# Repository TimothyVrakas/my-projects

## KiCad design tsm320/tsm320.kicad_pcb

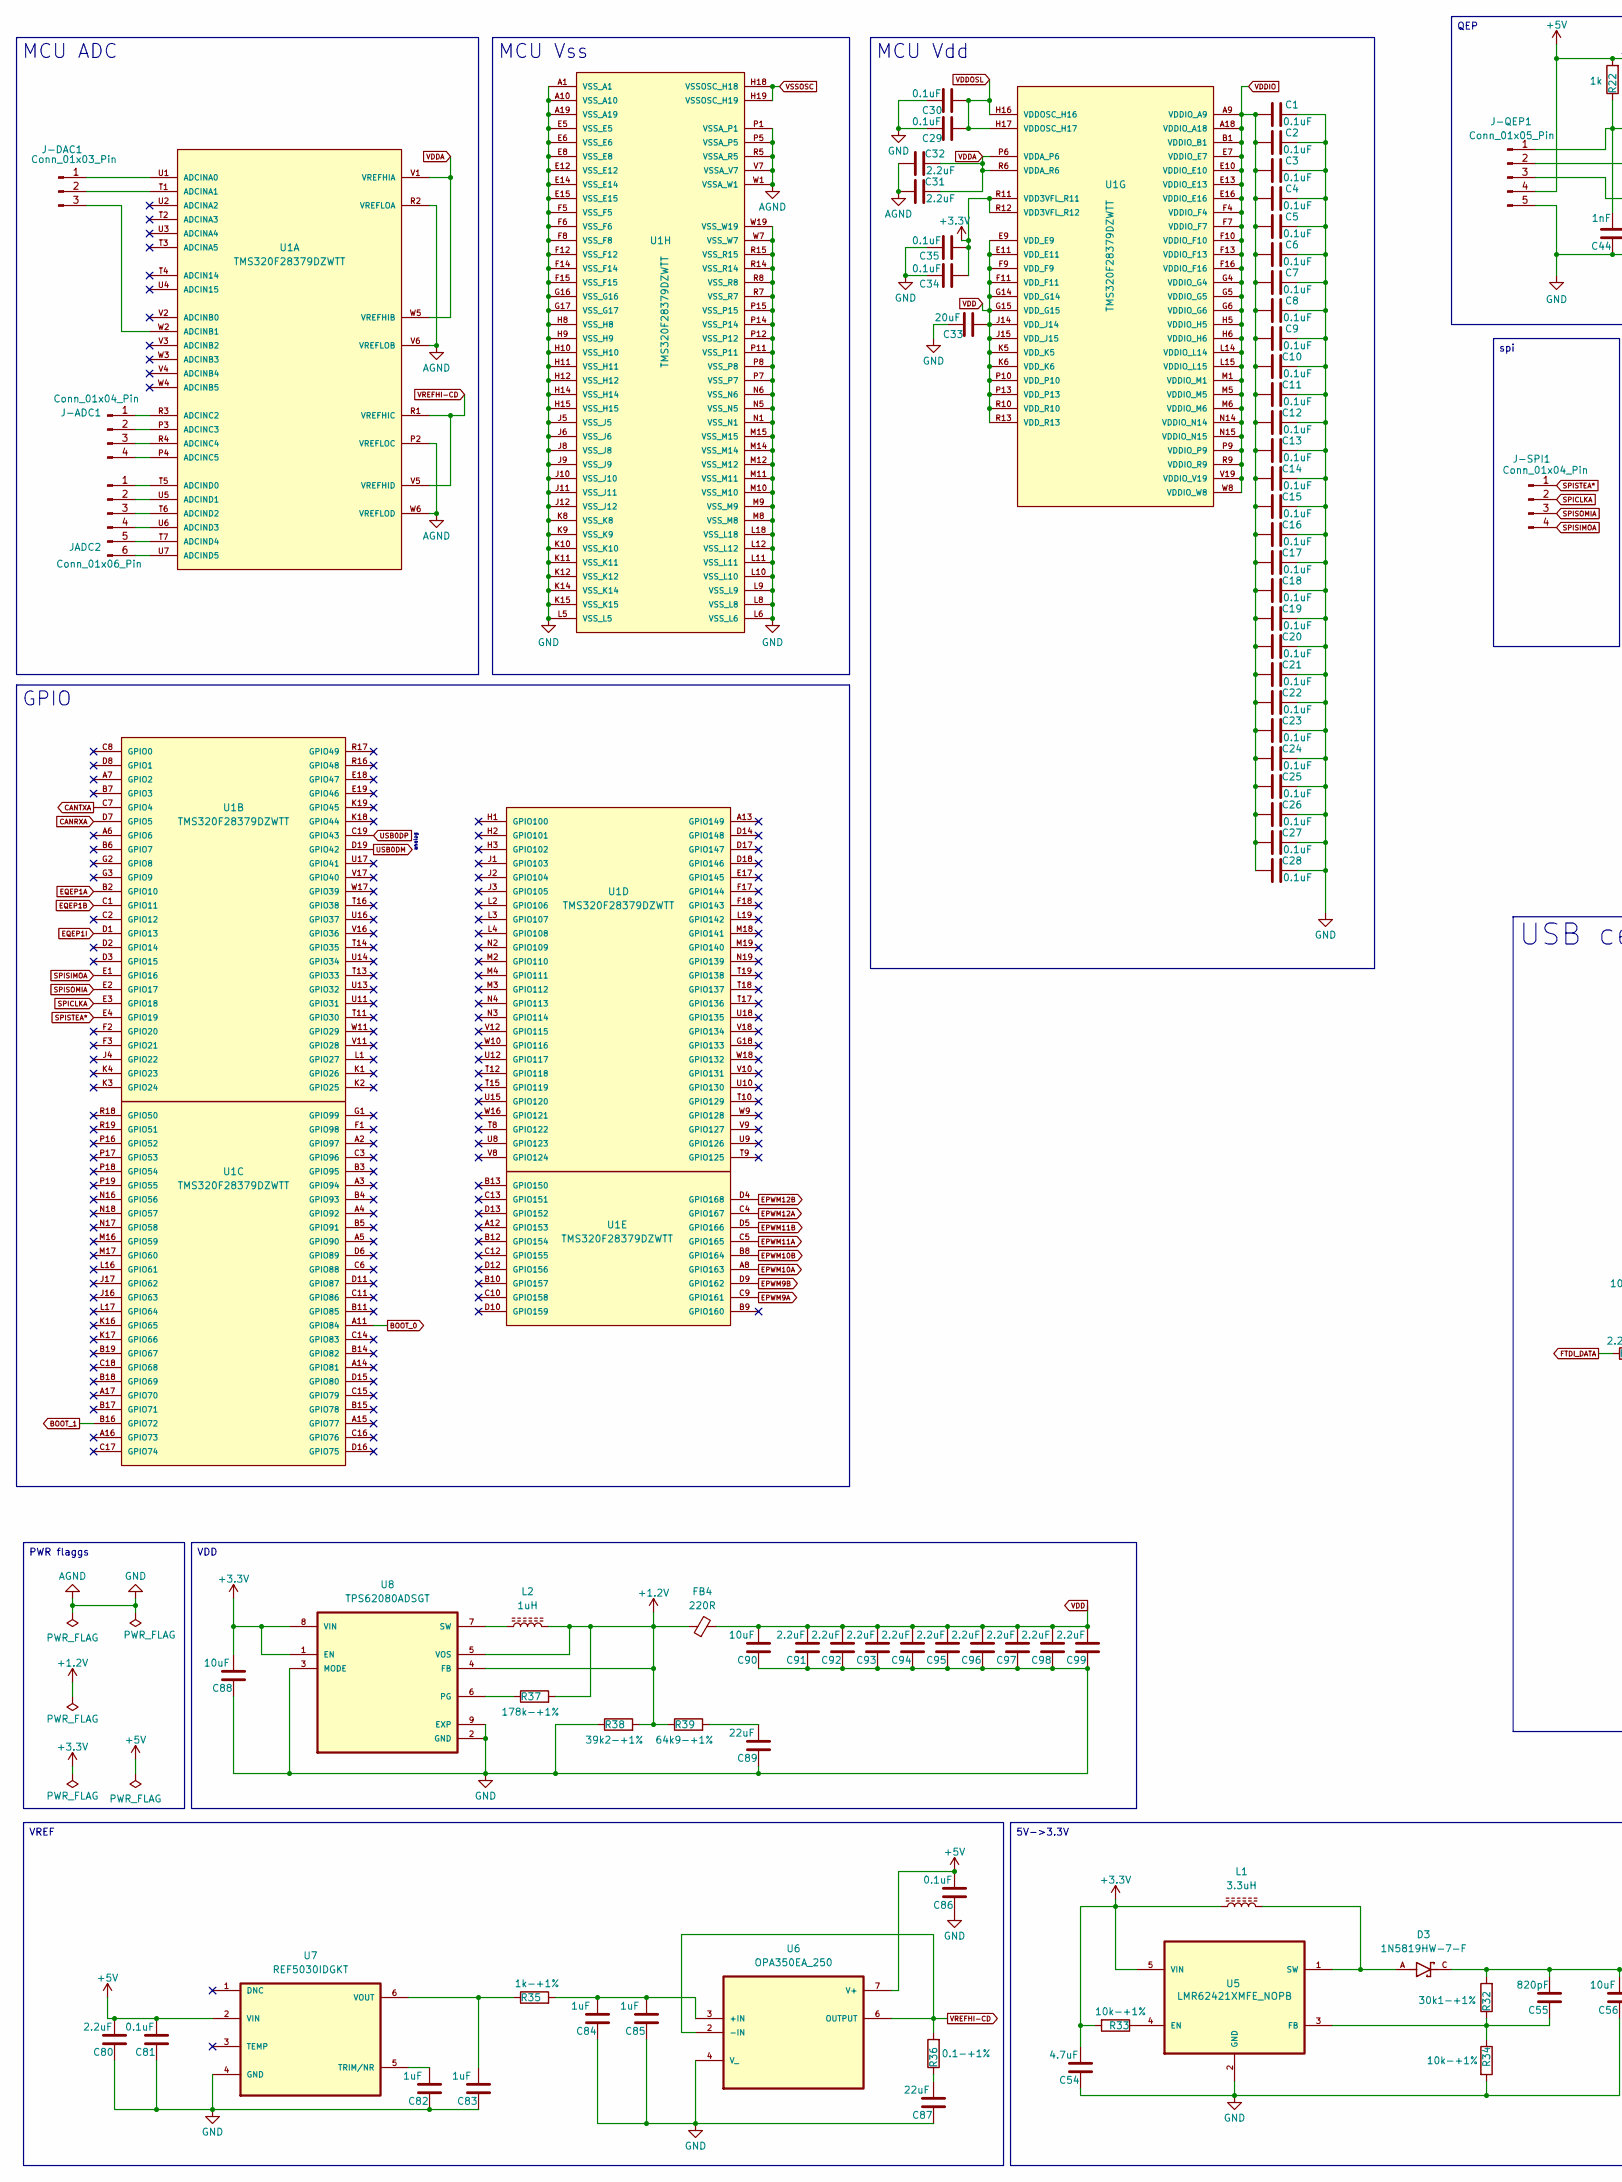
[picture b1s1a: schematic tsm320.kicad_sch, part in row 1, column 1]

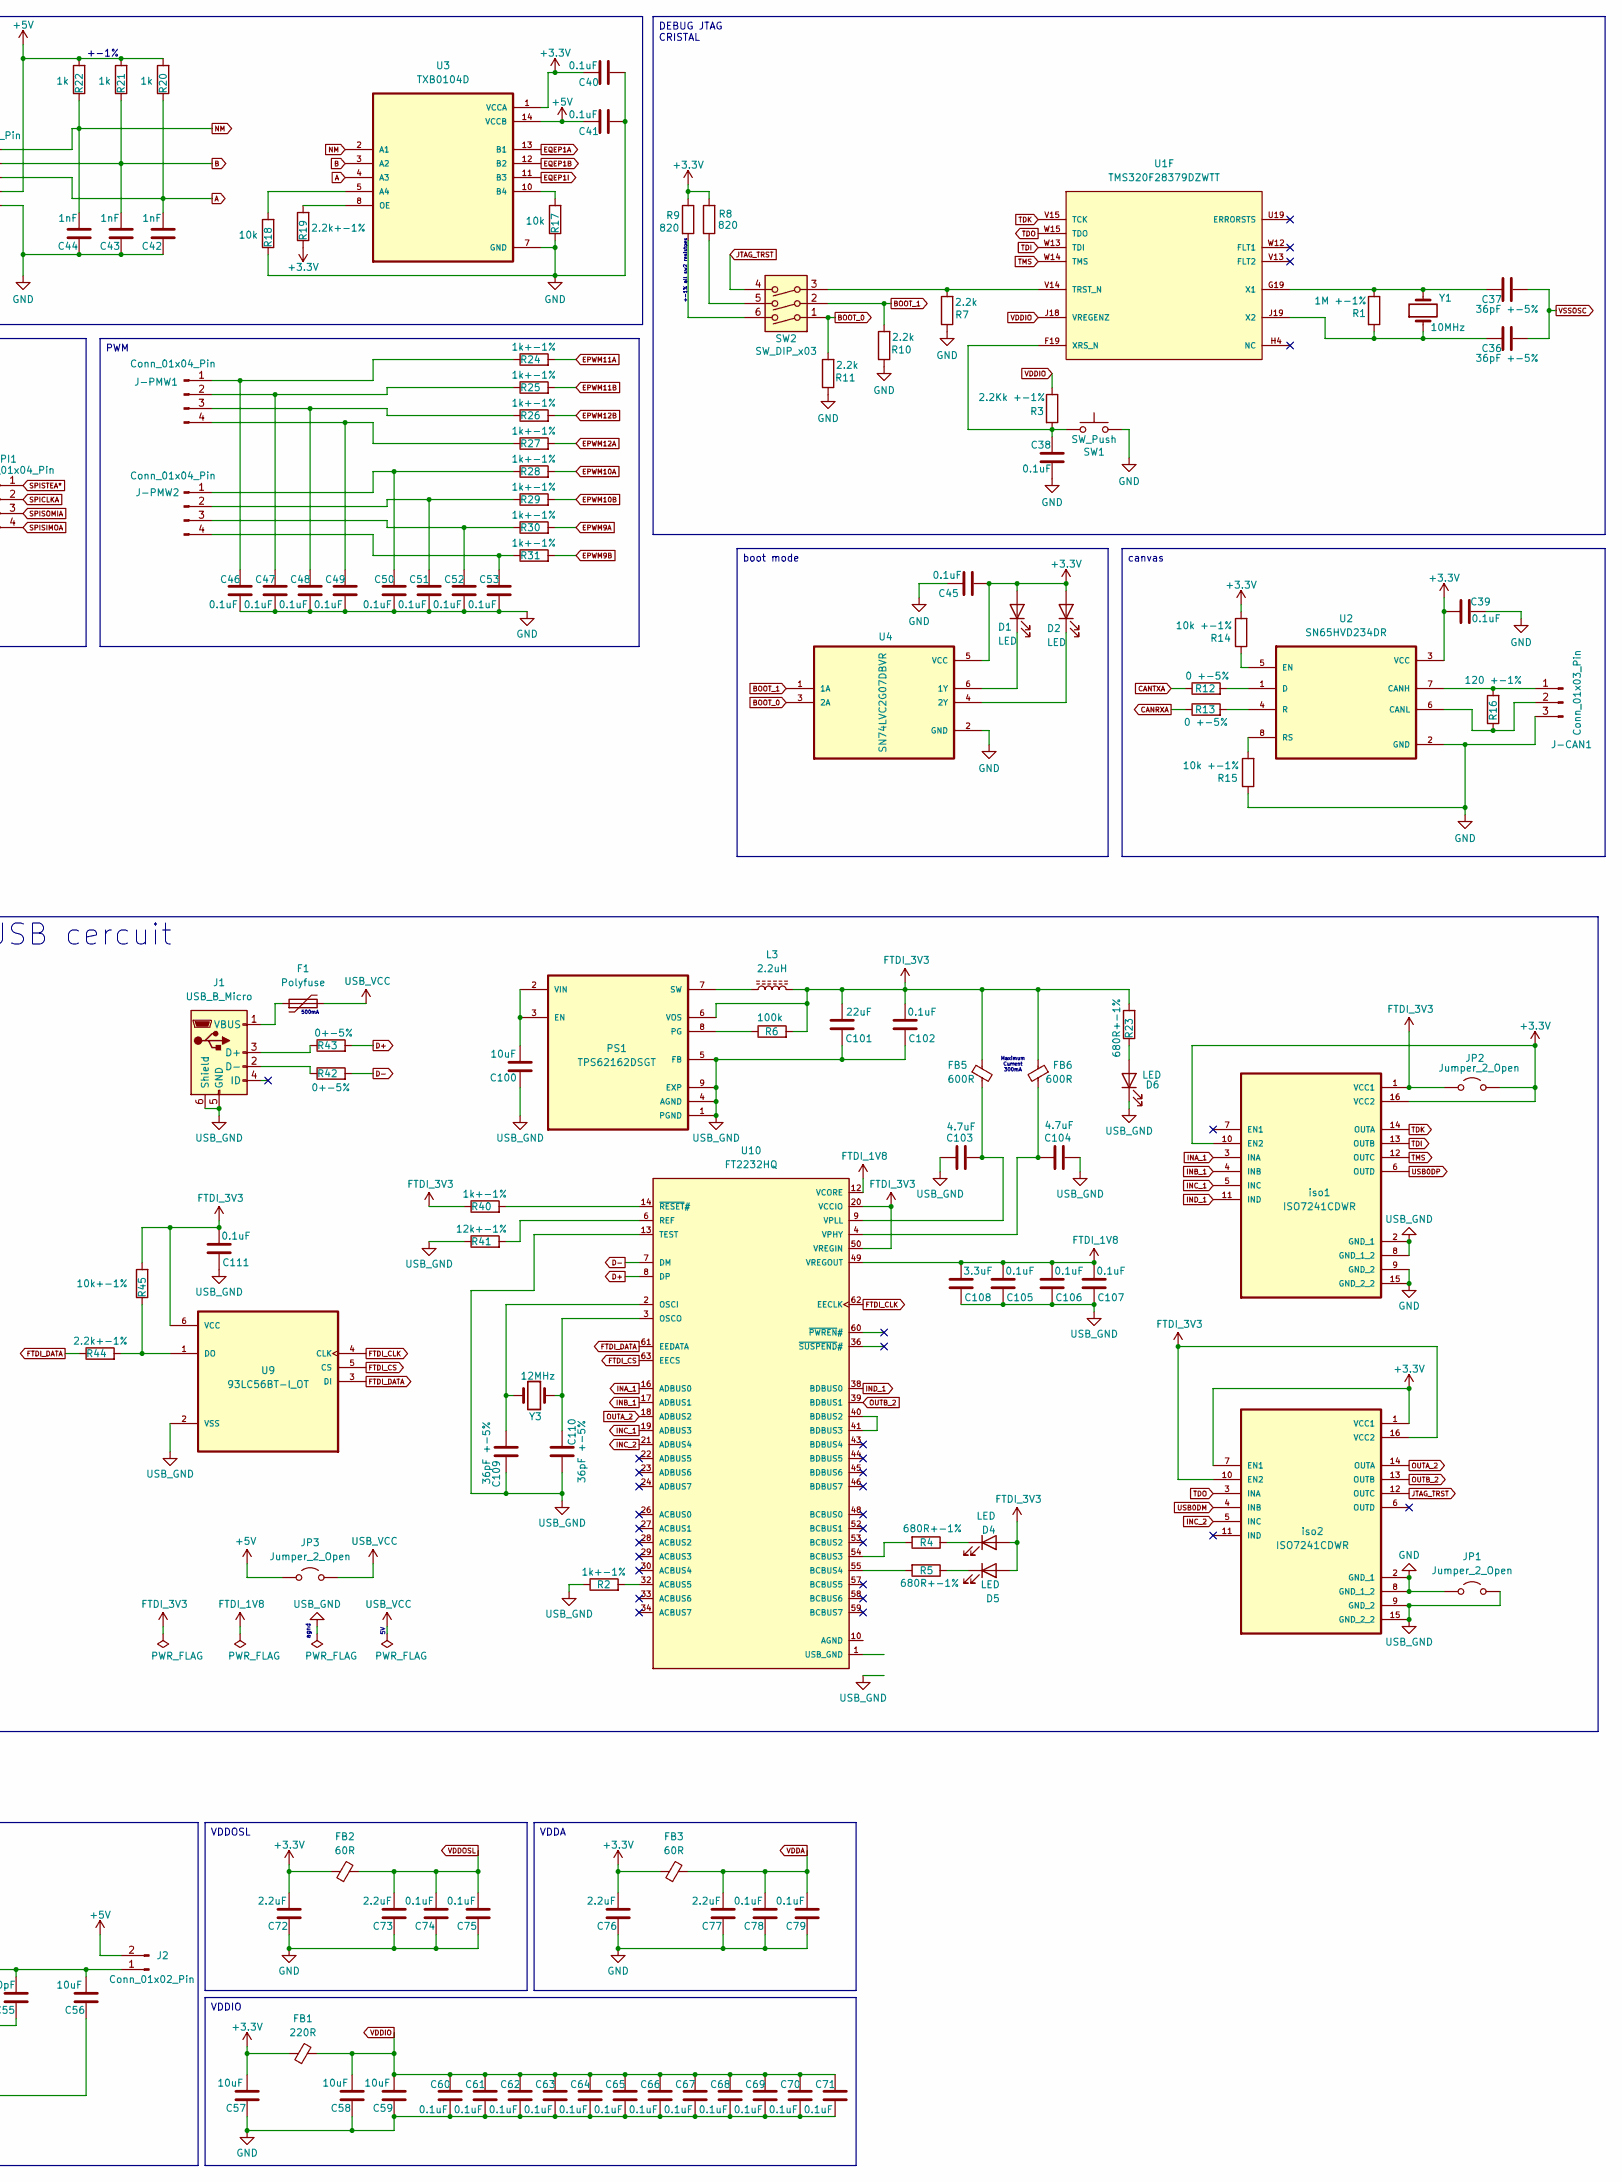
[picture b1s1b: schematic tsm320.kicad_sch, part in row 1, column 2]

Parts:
C1, C2, C3, C4, C5, C6, C7, C8, C9, C10, C11, C12, C13, C14, C15, C16, C17, C18, C19, C20, C21, C22, C23, C24, C25, C26, C27, C28, C29, C30, C34, C35, C38, C39, C40, C41, C45, C46, C47, C48, C49, C50, C51, C52, C53, C60, C61, C62, C63, C64, C65, C66, C67, C68, C69, C70, C71, C74, C75, C78, C79, C81, C86, C102, C105, C106, C107, C111: 0.1uF; C_0805_2012Metric_Pad1.18x1.45mm_HandSolder
C31, C32, C72, C73, C76, C77, C80, C91, C92, C93, C94, C95, C96, C97, C98, C99: 2.2uF; C_0805_2012Metric_Pad1.18x1.45mm_HandSolder
C33: 20uF; C_0805_2012Metric_Pad1.18x1.45mm_HandSolder
C36, C37, C109, C110: 36pF +-5%; C_0805_2012Metric_Pad1.18x1.45mm_HandSolder
C42, C43, C44: 1nF; C_0805_2012Metric_Pad1.18x1.45mm_HandSolder
C54, C103, C104: 4.7uF; C_0805_2012Metric_Pad1.18x1.45mm_HandSolder
C55: 820pF; C_0805_2012Metric_Pad1.18x1.45mm_HandSolder
C56, C57, C58, C59, C88, C90, C100: 10uF; C_0805_2012Metric_Pad1.18x1.45mm_HandSolder
C82, C83, C84, C85: 1uF; C_0805_2012Metric_Pad1.18x1.45mm_HandSolder
C87, C89, C101: 22uF; C_0805_2012Metric_Pad1.18x1.45mm_HandSolder
C108: 3.3uF; C_0805_2012Metric_Pad1.18x1.45mm_HandSolder
D1, D2, D4, D5, D6: LED; LED_0805_2012Metric_Pad1.15x1.40mm_HandSolder
D3: 1N5819HW-7-F; SOD3715X145N; PARTREV 18-2
F1: Polyfuse; FUSM4632X85
FB1, FB4: 220R; L_0805_2012Metric_Pad1.05x1.20mm_HandSolder
FB2, FB3: 60R; L_0805_2012Metric_Pad1.05x1.20mm_HandSolder
FB5, FB6: 600R; L_0805_2012Metric_Pad1.05x1.20mm_HandSolder
J1: USB_B_Micro; TE_1-1734328-2
J2: Conn_01x02_Pin; PinHeader_1x02_P2.54mm_Vertical
J-ADC1: Conn_01x04_Pin; PinHeader_1x04_P2.54mm_Vertical
J-CAN1: Conn_01x03_Pin; PinHeader_1x03_P2.54mm_Vertical
J-DAC1: Conn_01x03_Pin; PinHeader_1x03_P2.54mm_Vertical
J-PMW1, J-PMW2: Conn_01x04_Pin; PinHeader_1x04_P2.54mm_Vertical
J-QEP1: Conn_01x05_Pin; PinHeader_1x05_P2.54mm_Vertical
J-SPI1: Conn_01x04_Pin; PinHeader_1x04_P2.54mm_Vertical
JADC2: Conn_01x06_Pin; PinHeader_1x06_P2.54mm_Vertical
JP1, JP2, JP3: Jumper_2_Open; TestPoint_2Pads_Pitch2.54mm_Drill0.8mm
L1: 3.3uH; L_0805_2012Metric_Pad1.05x1.20mm_HandSolder
L2: 1uH; L_0805_2012Metric_Pad1.05x1.20mm_HandSolder
L3: 2.2uH; L_0805_2012Metric_Pad1.05x1.20mm_HandSolder
PS1: TPS62162DSGT; SON50P200X200X80-9N; PARTREV E
R1: 1M +-1%; R_0805_2012Metric_Pad1.20x1.40mm_HandSolder
R2, R24, R25, R26, R27, R28, R29, R30, R31, R40: 1k+-1%; R_0805_2012Metric_Pad1.20x1.40mm_HandSolder
R3: 2.2Kk +-1%; R_0805_2012Metric_Pad1.20x1.40mm_HandSolder
R4, R5, R23: 680R+-1%; R_0805_2012Metric_Pad1.20x1.40mm_HandSolder
R6: 100k; R_0805_2012Metric_Pad1.20x1.40mm_HandSolder
R7, R10, R11: 2.2k; R_0805_2012Metric_Pad1.20x1.40mm_HandSolder
R8, R9: 820; R_0805_2012Metric_Pad1.20x1.40mm_HandSolder
R12, R13: 0 +-5%; R_0805_2012Metric_Pad1.20x1.40mm_HandSolder
R14, R15: 10k +-1%; R_0805_2012Metric_Pad1.20x1.40mm_HandSolder
R16: 120 +-1%; R_0805_2012Metric_Pad1.20x1.40mm_HandSolder
R17, R18: 10k; R_0805_2012Metric_Pad1.20x1.40mm_HandSolder
R19, R44: 2.2k+-1%; R_0805_2012Metric_Pad1.20x1.40mm_HandSolder
R20, R21, R22: 1k; R_0805_2012Metric_Pad1.20x1.40mm_HandSolder
R32: 30k1-+1%; R_0805_2012Metric_Pad1.20x1.40mm_HandSolder
R33, R34: 10k-+1%; R_0805_2012Metric_Pad1.20x1.40mm_HandSolder
R35: 1k-+1%; R_0805_2012Metric_Pad1.20x1.40mm_HandSolder
R36: 0.1-+1%; R_0805_2012Metric_Pad1.20x1.40mm_HandSolder
R37: 178k-+1%; R_0805_2012Metric_Pad1.20x1.40mm_HandSolder
R38: 39k2-+1%; R_0805_2012Metric_Pad1.20x1.40mm_HandSolder
R39: 64k9-+1%; R_0805_2012Metric_Pad1.20x1.40mm_HandSolder
R41: 12k+-1%; R_0805_2012Metric_Pad1.20x1.40mm_HandSolder
R42, R43: 0+-5%; R_0805_2012Metric_Pad1.20x1.40mm_HandSolder
R45: 10k+-1%; R_0805_2012Metric_Pad1.20x1.40mm_HandSolder
SW1: SW_Push; B3F3152
SW2: SW_DIP_x03; SW3_219-3MST_CTS
U1: TMS320F28379DZWTT; BGA337C80P19X19_1600X1600X140N; PARTREV M; DigiKey_Part_Number 296-48453-ND
U2: SN65HVD234DR; SOIC127P600X175-8N
U3: TXB0104D; SOIC127P600X175-14N; DigiKey_Part_Number 296-34698-5-ND
U4: SN74LVC2G07DBVR; SOT95P280X145-6N
U5: LMR62421XMFE_NOPB; SOT95P280X145-5N
U6: OPA350EA_250; SOP65P490X110-8N
U7: REF5030IDGKT; SOP65P490X110-8N
U8: TPS62080ADSGT; SON50P200X200X80-9N; PARTREV F; DigiKey_Part_Number 296-30360-1-ND
U9: 93LC56BT-I_OT; SOT95P280X145-6N
U10: FT2232HQ; QFN50P900X900X100-65N
Y1: 10MHz; Crystal_SMD_HC49-SD_HandSoldering
Y3: 12MHz; Crystal_SMD_HC49-SD_HandSoldering
iso1, iso2: ISO7241CDWR; SOIC127P1030X265-16N

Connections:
+1.2V: FB4.1, L2.2, R37.2, R38.2, R39.1, U8.4 (FB), U8.5 (VOS)
+3.3V: C34.1, C35.1, C39.1, C40.2, C45.1, C54.2, C57.2, C72.2, C76.2, C88.2, D1.2 (A), D2.2 (A), FB1.1, FB2.1, FB3.1, JP2.2 (B), L1.1, R8.2, R9.1, R14.2, R19.1, R33.2, U1.R11 (VDD3VFL_R11), U1.R12 (VDD3VFL_R12), U2.3 (VCC), U3.1 (VCCA), U4.5 (VCC), U5.5 (VIN), U8.1 (EN), U8.8 (VIN), iso1.10 (EN2), iso1.16 (VCC2), iso2.1 (VCC1), iso2.7 (EN1)
+5V: C41.2, C80.2, C81.2, C86.2, J2.2, J-QEP1.4, JP3.1 (A), R20.2, R21.2, R22.2, U3.14 (VCCB), U6.7 (V+), U7.2 (VIN)
A: C42.2, J-QEP1.3, R20.1, U3.4 (A3)
AGND: C1.2, C2.2, C3.2, C4.2, C5.2, C6.2, C7.2, C8.2, C9.2, C10.2, C11.2, C12.2, C13.2, C14.2, C15.2, C16.2, C17.2, C18.2, C19.2, C20.2, C21.2, C22.2, C23.2, C24.2, C25.2, C26.2, C27.2, C28.2, C29.2, C30.2, C31.1, C32.1, C33.2, C34.2, C35.2, C38.1, C39.2, C40.1, C41.1, C42.1, C43.1, C44.1, C45.2, C46.2, C47.2, C48.2, C49.2, C50.2, C51.2, C52.2, C53.2, C54.1, C56.1, C57.1, C58.1, C59.1, C60.2, C61.2, C62.2, C63.2, C64.2, C65.2, C66.2, C67.2, C68.2, C69.2, C70.2, C71.2, C72.1, C73.1, C74.1, C75.1, C76.1, C77.1, C78.1, C79.1, C80.1, C81.1, C82.1, C83.1, C84.1, C85.1, C86.1, C87.1, C88.1, C89.1, C90.1, C91.1, C92.1, C93.1, C94.1, C95.1, C96.1, C97.1, C98.1, C99.1, J-CAN1.3 (Pin_1), J-QEP1.5, JP1.1 (A), R7.1, R10.1, R11.1, R15.1, R17.1, R18.1, R34.2, R38.1, SW1.2, U1.A1 (VSS_A1), U1.A10 (VSS_A10), U1.A19 (VSS_A19), U1.E5 (VSS_E5), U1.E6 (VSS_E6), U1.E8 (VSS_E8), U1.E12 (VSS_E12), U1.E14 (VSS_E14), U1.E15 (VSS_E15), U1.F5 (VSS_F5), U1.F6 (VSS_F6), U1.F8 (VSS_F8), U1.F12 (VSS_F12), U1.F14 (VSS_F14), U1.F15 (VSS_F15), U1.G16 (VSS_G16), U1.G17 (VSS_G17), U1.H8 (VSS_H8), U1.H9 (VSS_H9), U1.H10 (VSS_H10), U1.H11 (VSS_H11), U1.H12 (VSS_H12), U1.H14 (VSS_H14), U1.H15 (VSS_H15), U1.J5 (VSS_J5), U1.J6 (VSS_J6), U1.J8 (VSS_J8), U1.J9 (VSS_J9), U1.J10 (VSS_J10), U1.J11 (VSS_J11), U1.J12 (VSS_J12), U1.K8 (VSS_K8), U1.K9 (VSS_K9), U1.K10 (VSS_K10), U1.K11 (VSS_K11), U1.K12 (VSS_K12), U1.K14 (VSS_K14), U1.K15 (VSS_K15), U1.L5 (VSS_L5), U1.L6 (VSS_L6), U1.L8 (VSS_L8), U1.L9 (VSS_L9), U1.L10 (VSS_L10), U1.L11 (VSS_L11), U1.L12 (VSS_L12), U1.L18 (VSS_L18), U1.M8 (VSS_M8), U1.M9 (VSS_M9), U1.M10 (VSS_M10), U1.M11 (VSS_M11), U1.M12 (VSS_M12), U1.M14 (VSS_M14), U1.M15 (VSS_M15), U1.N1 (VSS_N1), U1.N5 (VSS_N5), U1.N6 (VSS_N6), U1.P1 (VSSA_P1), U1.P2 (VREFLOC), U1.P5 (VSSA_P5), U1.P7 (VSS_P7), U1.P8 (VSS_P8), U1.P11 (VSS_P11), U1.P12 (VSS_P12), U1.P14 (VSS_P14), U1.P15 (VSS_P15), U1.R2 (VREFLOA), U1.R5 (VSSA_R5), U1.R7 (VSS_R7), U1.R8 (VSS_R8), U1.R14 (VSS_R14), U1.R15 (VSS_R15), U1.V6 (VREFLOB), U1.V7 (VSSA_V7), U1.W1 (VSSA_W1), U1.W6 (VREFLOD), U1.W7 (VSS_W7), U1.W19 (VSS_W19), U2.2 (GND), U3.7 (GND), U4.2 (GND), U5.2 (GND), U6.4 (V_), U7.4 (GND), U8.2 (GND), U8.3 (MODE), U8.9 (EXP), U8.10, U8.11, iso1.9 (GND_2), iso1.15 (GND_2_2), iso2.2 (GND_1), iso2.8 (GND_1_2)
B: C43.2, J-QEP1.2, R21.1, U3.3 (A2)
BOOT_0: R11.2, SW2.1, U1.A11 (GPIO84), U4.3 (2A)
BOOT_1: R10.2, SW2.2, U1.B16 (GPIO72), U4.1 (1A)
CANRXA: R13.1, U1.D7 (GPIO5)
CANTXA: R12.1, U1.C7 (GPIO4)
D+: R43.2, U10.8 (DP)
D-: R42.2, U10.7 (DM)
EPWM9A: R30.2, U1.C9 (GPIO161)
EPWM9B: R31.2, U1.D9 (GPIO162)
EPWM10A: R28.2, U1.A8 (GPIO163)
EPWM10B: R29.2, U1.B8 (GPIO164)
EPWM11A: R24.2, U1.C5 (GPIO165)
EPWM11B: R25.2, U1.D5 (GPIO166)
EPWM12A: R27.2, U1.C4 (GPIO167)
EPWM12B: R26.2, U1.D4 (GPIO168)
EQEP1A: U1.B2 (GPIO10), U3.13 (B1)
EQEP1B: U1.C1 (GPIO11), U3.12 (B2)
EQEP1I: U1.D1 (GPIO13), U3.11 (B3)
FTDI_1V8: C105.2, C106.2, C107.2, C108.2, U10.12 (VCORE), U10.37 (VCORE), U10.49 (VREGOUT), U10.64 (VCORE)
FTDI_3V3: C101.2, C102.2, C111.2, D4.2 (A), D5.2 (A), FB5.1, FB6.1, JP2.1 (A), L3.2, PS1.6 (VOS), R6.2, R23.2, R40.1, R45.2, U9.6 (VCC), U10.20 (VCCIO), U10.31 (VCCIO), U10.42 (VCCIO), U10.50 (VREGIN), U10.56 (VCCIO), iso1.1 (VCC1), iso2.10 (EN2), iso2.16 (VCC2)
FTDI_CLK: U9.4 (CLK), U10.62 (EECLK)
FTDI_CS: U9.5 (CS), U10.63 (EECS)
FTDI_DATA: R44.1, U9.3 (DI), U10.61 (EEDATA)
INA_1: U10.16 (ADBUS0), iso1.3 (INA)
INB_1: U10.17 (ADBUS1), iso1.4 (INB)
INC_1: U10.19 (ADBUS3), iso1.5 (INC)
INC_2: U10.21 (ADBUS4), iso2.5 (INC)
IND_1: U10.38 (BDBUS0), iso1.11 (IND)
JTAG_TRST: SW2.4, iso2.12 (OUTC)
NM: C44.2, J-QEP1.1, R22.1, U3.2 (A1)
unnamed: C87.2, R36.1
unnamed: C89.2, R39.2
unnamed: D1.1 (K), U4.6 (1Y)
unnamed: D2.1 (K), U4.4 (2Y)
unnamed: D4.1 (K), R4.1
unnamed: D5.1 (K), R5.1
unnamed: D6.2 (A), R23.1
unnamed: J1.3 (D+), R43.1
unnamed: J1.2 (D-), R42.1
unnamed: F1.1, J1.1 (VBUS)
unnamed: C55.2, C56.2, D3.C, J2.1, R32.2
unnamed: J-ADC1.1, U1.R3 (ADCINC2)
unnamed: J-ADC1.2, U1.P3 (ADCINC3)
unnamed: J-ADC1.3, U1.R4 (ADCINC4)
unnamed: J-ADC1.4, U1.P4 (ADCINC5)
unnamed: J-CAN1.2, R16.1, U2.6 (CANL)
unnamed: J-CAN1.1 (Pin_3), R16.2, U2.7 (CANH)
unnamed: J-DAC1.1, U1.U1 (ADCINA0)
unnamed: J-DAC1.2, U1.T1 (ADCINA1)
unnamed: J-DAC1.3, U1.W2 (ADCINB1)
unnamed: C46.1, J-PMW1.1, R24.1
unnamed: C47.1, J-PMW1.2, R25.1
unnamed: C48.1, J-PMW1.3, R26.1
unnamed: C49.1, J-PMW1.4, R27.1
unnamed: C50.1, J-PMW2.1, R28.1
unnamed: C51.1, J-PMW2.2, R29.1
unnamed: C52.1, J-PMW2.3, R30.1
unnamed: C53.1, J-PMW2.4, R31.1
unnamed: JADC2.1, U1.T5 (ADCIND0)
unnamed: JADC2.2, U1.U5 (ADCIND1)
unnamed: JADC2.3, U1.T6 (ADCIND2)
unnamed: JADC2.4, U1.U6 (ADCIND3)
unnamed: JADC2.5, U1.T7 (ADCIND4)
unnamed: JADC2.6, U1.U7 (ADCIND5)
unnamed: C100.2, PS1.2 (VIN), PS1.3 (EN)
unnamed: PS1.8 (PG), R6.1
unnamed: L3.1, PS1.7 (SW)
unnamed: R8.1, SW2.5
unnamed: R9.2, SW2.6
unnamed: R7.2, SW2.3, U1.V14 (TRST_N)
unnamed: C37.2, R1.1, U1.G19 (X1), Y1.2
unnamed: C36.2, R1.2, U1.J19 (X2), Y1.1
unnamed: C38.2, R3.2, SW1.1, U1.F19 (XRS_N)
unnamed: R12.2, U2.1 (D)
unnamed: R14.1, U2.5 (EN)
unnamed: R13.2, U2.4 (R)
unnamed: R15.2, U2.8 (RS)
unnamed: R18.2, U3.5 (A4)
unnamed: R17.2, U3.10 (B4)
unnamed: R19.2, U3.8 (OE)
unnamed: R33.1, U5.4 (EN)
unnamed: C55.1, R32.1, R34.1, U5.3 (FB)
unnamed: D3.A, L1.2, U5.1 (SW)
unnamed: C84.2, C85.2, R35.2, U6.3 (+IN)
unnamed: C82.2, U7.5 (TRIM/NR)
unnamed: C83.2, R35.1, U7.6 (VOUT)
unnamed: R37.1, U8.6 (PG)
unnamed: L2.1, U8.7 (SW)
unnamed: R44.2, R45.1, U9.1 (DO)
unnamed: R2.2, U10.32 (ACBUS5)
unnamed: R4.2, U10.54 (BCBUS3)
unnamed: R5.2, U10.55 (BCBUS4)
unnamed: U10.40 (BDBUS2), U10.41 (BDBUS3)
unnamed: C109.2, U10.2 (OSCI), Y3.2
unnamed: C110.2, U10.3 (OSCO), Y3.1
unnamed: R41.2, U10.6 (REF)
unnamed: C104.2, FB6.2, U10.4 (VPHY)
unnamed: C103.1, FB5.2, U10.9 (VPLL)
unnamed: R40.2, U10.14 (~RESET#)
OUTA_2: U10.18 (ADBUS2), iso2.14 (OUTA)
OUTB_2: U10.39 (BDBUS1), iso2.13 (OUTB)
SPICLKA: J-SPI1.2, U1.E3 (GPIO18)
SPISIMOA: J-SPI1.4, U1.E1 (GPIO16)
SPISOMIA: J-SPI1.3, U1.E2 (GPIO17)
SPISTEA*: J-SPI1.1, U1.E4 (GPIO19)
TDI: U1.W13 (TDI), iso1.13 (OUTB)
TDK: U1.V15 (TCK), iso1.14 (OUTA)
TDO: U1.W15 (TDO), iso2.3 (INA)
TMS: U1.W14 (TMS), iso1.12 (OUTC)
USB0DM: U1.D19 (GPIO42), iso2.4 (INB)
USB0DP: U1.C19 (GPIO43), iso1.6 (OUTD)
USB_VCC: F1.2, JP3.2 (B)
VDD: C33.1, C90.2, C91.2, C92.2, C93.2, C94.2, C95.2, C96.2, C97.2, C98.2, C99.2, FB4.2, U1.E9 (VDD_E9), U1.E11 (VDD_E11), U1.F9 (VDD_F9), U1.F11 (VDD_F11), U1.G14 (VDD_G14), U1.G15 (VDD_G15), U1.J14 (VDD_J14), U1.J15 (VDD_J15), U1.K5 (VDD_K5), U1.K6 (VDD_K6), U1.P10 (VDD_P10), U1.P13 (VDD_P13), U1.R10 (VDD_R10), U1.R13 (VDD_R13)
VDDA: C31.2, C32.2, C77.2, C78.2, C79.2, FB3.2, U1.P6 (VDDA_P6), U1.R6 (VDDA_R6), U1.V1 (VREFHIA), U1.W5 (VREFHIB)
VDDIO: C1.1, C2.1, C3.1, C4.1, C5.1, C6.1, C7.1, C8.1, C9.1, C10.1, C11.1, C12.1, C13.1, C14.1, C15.1, C16.1, C17.1, C18.1, C19.1, C20.1, C21.1, C22.1, C23.1, C24.1, C25.1, C26.1, C27.1, C28.1, C58.2, C59.2, C60.1, C61.1, C62.1, C63.1, C64.1, C65.1, C66.1, C67.1, C68.1, C69.1, C70.1, C71.1, FB1.2, R3.1, U1.A9 (VDDIO_A9), U1.A18 (VDDIO_A18), U1.B1 (VDDIO_B1), U1.E7 (VDDIO_E7), U1.E10 (VDDIO_E10), U1.E13 (VDDIO_E13), U1.E16 (VDDIO_E16), U1.F4 (VDDIO_F4), U1.F7 (VDDIO_F7), U1.F10 (VDDIO_F10), U1.F13 (VDDIO_F13), U1.F16 (VDDIO_F16), U1.G4 (VDDIO_G4), U1.G5 (VDDIO_G5), U1.G6 (VDDIO_G6), U1.H5 (VDDIO_H5), U1.H6 (VDDIO_H6), U1.J18 (VREGENZ), U1.L14 (VDDIO_L14), U1.L15 (VDDIO_L15), U1.M1 (VDDIO_M1), U1.M5 (VDDIO_M5), U1.M6 (VDDIO_M6), U1.N14 (VDDIO_N14), U1.N15 (VDDIO_N15), U1.P9 (VDDIO_P9), U1.R9 (VDDIO_R9), U1.V19 (VDDIO_V19), U1.W8 (VDDIO_W8)
VDDOSL: C29.1, C30.1, C73.2, C74.2, C75.2, FB2.2, U1.H16 (VDDOSC_H16), U1.H17 (VDDOSC_H17)
VREFHI-CD: R36.2, U1.R1 (VREFHIC), U1.V5 (VREFHID), U6.2 (-IN), U6.6 (OUTPUT)
VSSOSC: C36.1, C37.1, U1.H18 (VSSOSC_H18), U1.H19 (VSSOSC_H19)

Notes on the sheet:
agnd
Maximum Current 300mA
500mA
analog
+-1%
+-1% all sw2 resistoes
MCU ADC
PWM
spi
VDDA
PWR flaggs
VDD
5V->3.3V
DEBUG JTAG CRISTAL
VDDOSL
canvas
QEP
USB cercuit
GPIO
MCU Vdd
VREF
boot mode
MCU Vss
VDDIO

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
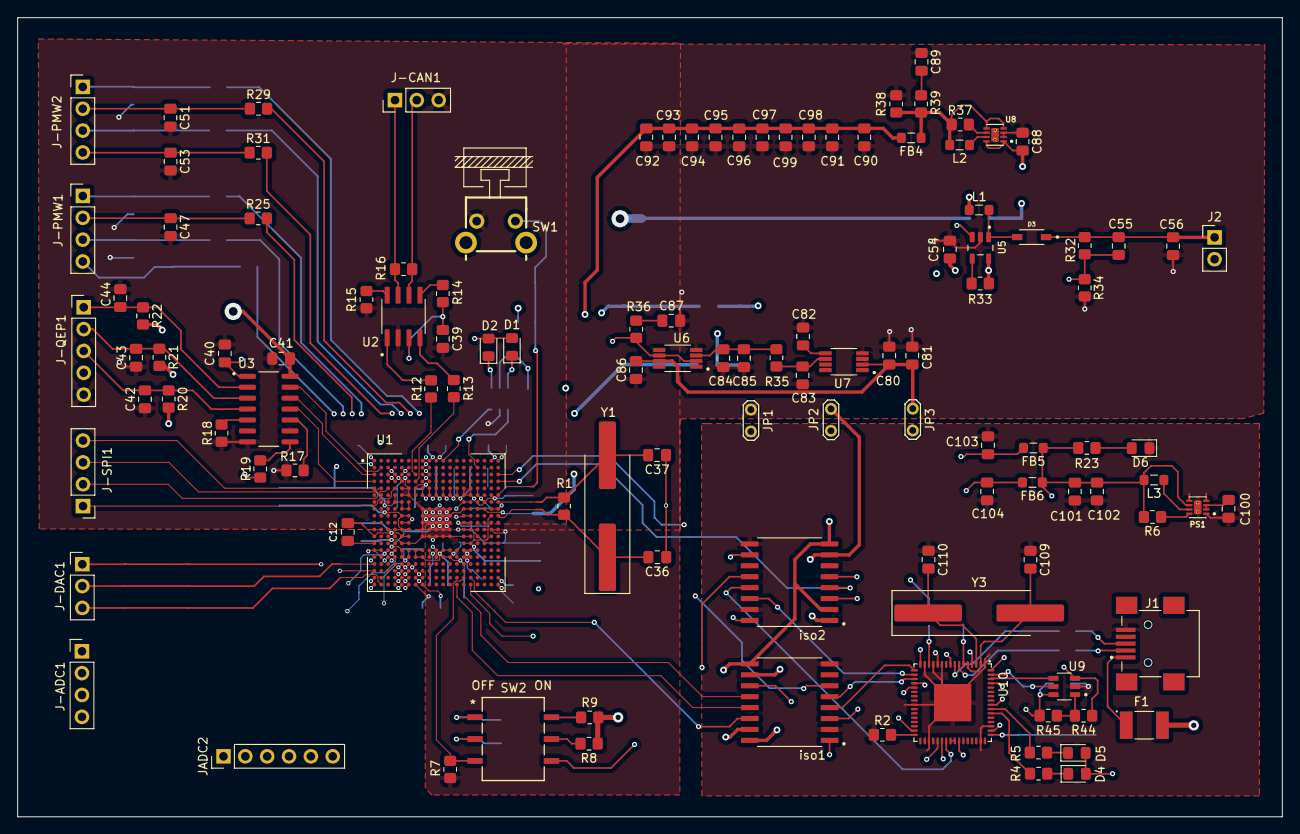
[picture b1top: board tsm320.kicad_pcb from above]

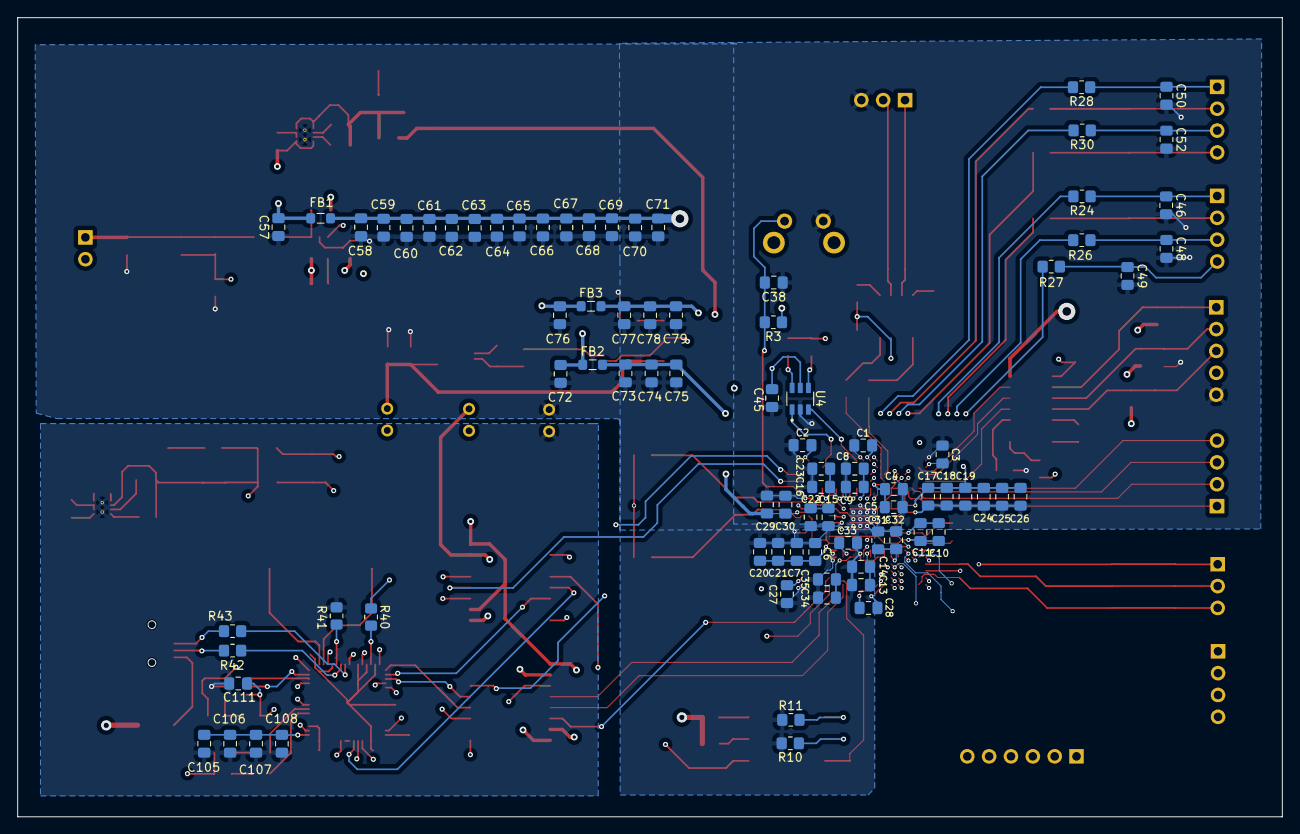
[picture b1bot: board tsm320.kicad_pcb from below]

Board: 6 copper layers, 147.0 x 92.9 mm, 202 parts (85 on the bottom side), 124 nets.

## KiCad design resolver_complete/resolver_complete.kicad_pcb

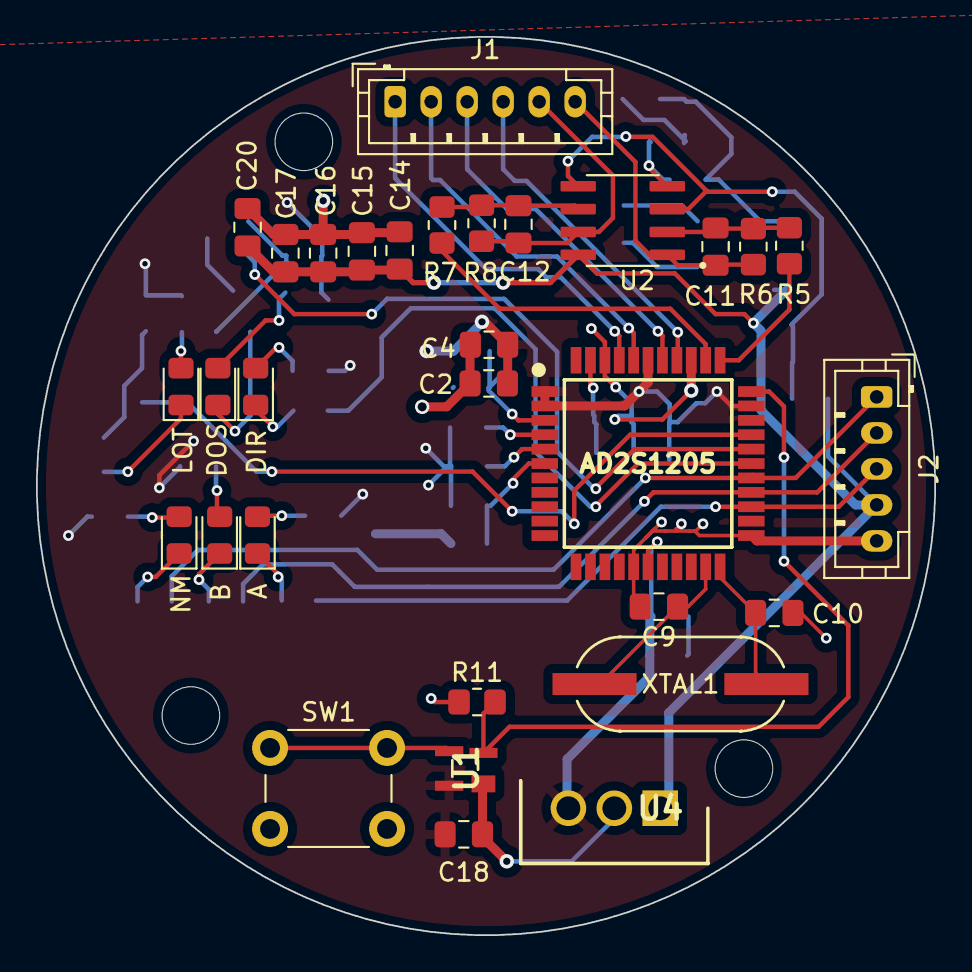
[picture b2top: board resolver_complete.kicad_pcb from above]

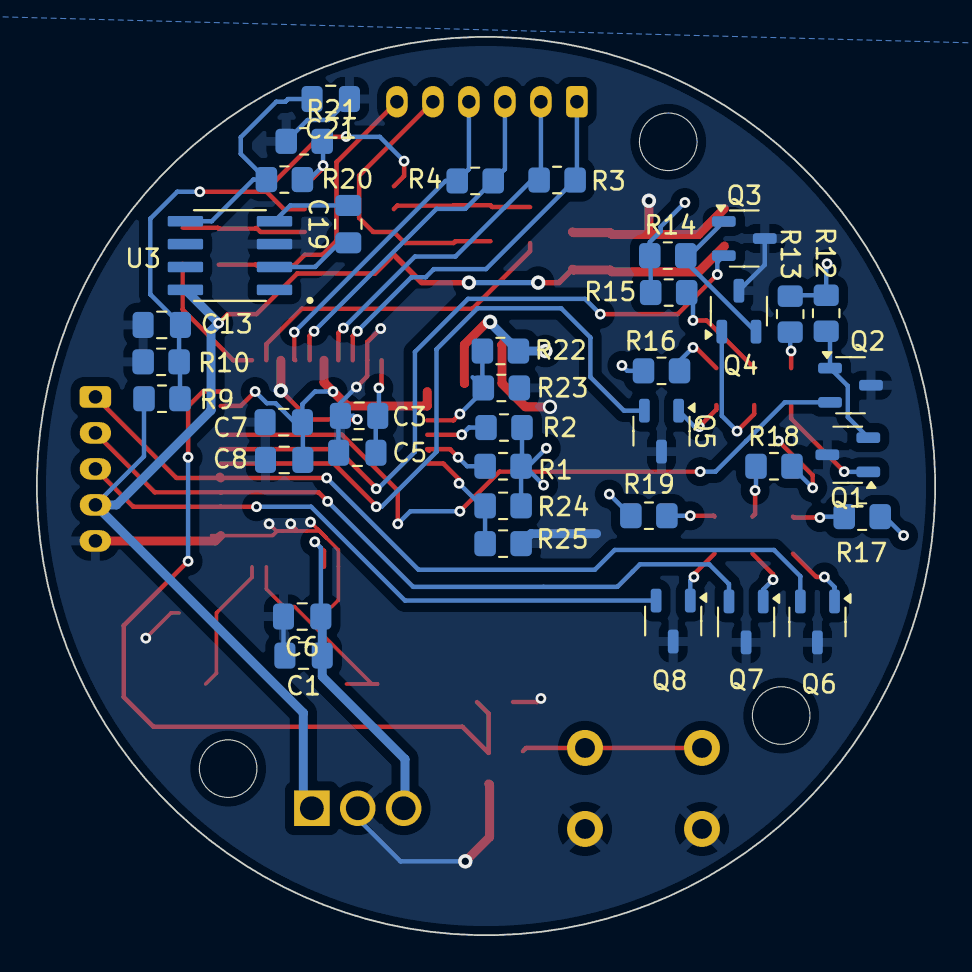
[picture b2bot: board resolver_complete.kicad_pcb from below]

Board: 2 copper layers, 49.9 x 49.9 mm, 69 parts (38 on the bottom side), 47 nets.

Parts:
A: LED; D_0805_2012Metric_Pad1.15x1.40mm_HandSolder
AD2S1205: AD2S1205YSTZ; QFP80P1200X1200X160-44N
B: LED; D_0805_2012Metric_Pad1.15x1.40mm_HandSolder
C1, C2, C5, C7, C19, C21: 10uF; C_0805_2012Metric_Pad1.18x1.45mm_HandSolder
C3, C4, C6, C8, C14, C15: 10nF; C_0805_2012Metric_Pad1.18x1.45mm_HandSolder
C9, C10: 22pF; C_0805_2012Metric_Pad1.18x1.45mm_HandSolder
C11, C12: 120pF; C_0805_2012Metric_Pad1.18x1.45mm_HandSolder
C13, C18, C20: 0.1uF; C_0805_2012Metric_Pad1.18x1.45mm_HandSolder
C16, C17: 1uF; C_0805_2012Metric_Pad1.18x1.45mm_HandSolder
DIR: LED; D_0805_2012Metric_Pad1.15x1.40mm_HandSolder
DOS: LED; D_0805_2012Metric_Pad1.15x1.40mm_HandSolder
J1: Conn_01x06_Pin; JST_PH_B6B-PH-K_1x06_P2.00mm_Vertical
J2: Conn_01x05_Pin; JST_PH_B5B-PH-K_1x05_P2.00mm_Vertical
LOT: LED; D_0805_2012Metric_Pad1.15x1.40mm_HandSolder
NM: LED; D_0805_2012Metric_Pad1.15x1.40mm_HandSolder
Q1, Q2, Q3, Q4, Q5, Q6, Q7, Q8: NPN; SOT-23-3
R1, R2, R5, R7, R10, R11, R12, R14: 10k; R_0805_2012Metric_Pad1.20x1.40mm_HandSolder
R3, R4: 68k; R_0805_2012Metric_Pad1.20x1.40mm_HandSolder
R6, R8: 15k4; R_0805_2012Metric_Pad1.20x1.40mm_HandSolder
R9: 22k; R_0805_2012Metric_Pad1.20x1.40mm_HandSolder
R13, R15, R16, R17, R18, R19: 2k2; R_0805_2012Metric_Pad1.20x1.40mm_HandSolder
R20, R21, R22, R23, R24, R25: 0; R_0805_2012Metric_Pad1.20x1.40mm_HandSolder
SW1: SW_Push; SW_PUSH_6mm_H4.3mm
U1: ADM811TARTZ-REEL7; ADM811RARTZREEL7
U2: AD8397; SOIC127P600X175-8N
U3: ICL7660; SOIC127P600X175-8N
U4: 7805; TO255P460X1020X2008-3P
XTAL1: ABLS-8.192MHZ-B2-T; XTAL_HC&slash_49US_ABLS_ABR

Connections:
+5VA: AD2S1205.1 (DVDD_1), AD2S1205.2 (~RD), AD2S1205.17 (DVDD_2), AD2S1205.31 (FS1), AD2S1205.32 (FS2), AD2S1205.39 (AVDD), C1.1, C2.1, C4.1, C6.1, C7.2, C8.2, C18.1, R1.1, R2.1, R12.2, R13.2, R14.2, R15.2, R16.2, R17.2, R18.2, R19.2, R22.2, R24.2, U1.4 (VCC), U4.3 (OUT)
-IN_1: C11.2, R5.2, R6.1, U2.2 (-IN_1)
-IN_2: C12.2, R7.2, R8.1, U2.6 (-IN_2)
A: AD2S1205.25 (A), J2.3, Q8.2 (B)
AGND: AD2S1205.16 (DGND_1), AD2S1205.23 (DGND_2), AD2S1205.36 (AGND_1), AD2S1205.42 (AGND_2), C1.2, C2.2, C3.1, C4.2, C5.2, C6.2, C7.1, C8.1, C9.2, C10.2, C13.1, C14.1, C15.1, C16.1, C17.1, C18.2, C20.1, C21.1, J2.5, Q1.3 (E), Q2.3 (E), Q3.3 (E), Q4.3 (E), Q5.3 (E), Q6.3 (E), Q7.3 (E), Q8.3 (E), R10.1, R11.1, R21.2, R23.2, R25.2, SW1.2, U1.1 (GND), U3.3 (GND), U4.2 (GND)
B: AD2S1205.26 (B), J2.2, Q7.2 (B)
COS+: AD2S1205.41 (COS), J1.1, R3.1
COS-: AD2S1205.40 (COSLO), J1.2, R3.2
DIR: AD2S1205.28 (DIR), Q5.2 (B)
DOS: AD2S1205.29 (DOS), Q3.2 (B)
EXC+: C11.1, J1.6, R6.2, U2.1 (OUT_1)
EXC+_MCU: AD2S1205.34 (EXC), R5.1
EXC-: C12.1, J1.5, R8.2, U2.7 (OUT_2)
EXC-_MCU: AD2S1205.35 (~EXC), R7.1
LOT: AD2S1205.30 (LOT), Q2.2 (B)
NM: AD2S1205.27 (NM), J2.1, Q6.2 (B)
unnamed: LOT.2 (A), R13.1
unnamed: LOT.1 (K), Q1.1 (C)
unnamed: DOS.2 (A), R15.1
unnamed: DOS.1 (K), Q4.1 (C)
unnamed: DIR.2 (A), R16.1
unnamed: DIR.1 (K), Q5.1 (C)
unnamed: NM.2 (A), R17.1
unnamed: NM.1 (K), Q6.1 (C)
unnamed: B.2 (A), R18.1
unnamed: B.1 (K), Q7.1 (C)
unnamed: A.2 (A), R19.1
unnamed: A.1 (K), Q8.1 (C)
unnamed: AD2S1205.22 (CLKIN), C10.1, XTAL1.2
unnamed: AD2S1205.43 (REFBYP), C3.2, C5.1
unnamed: AD2S1205.21 (XTALOUT), C9.1, XTAL1.1
unnamed: AD2S1205.3 (~CS), R22.1, R23.1
unnamed: AD2S1205.5 (~RDVEL), R1.2
unnamed: AD2S1205.4 (~SAMPLE), R2.2
unnamed: AD2S1205.6 (~SOE), R24.1, R25.1
unnamed: Q1.2 (B), Q2.1 (C), R12.1
unnamed: Q3.1 (C), Q4.2 (B), R14.1
unnamed: SW1.1, U1.3 (MR*)
unnamed: R20.1, R21.1, U2.4 (V-)
unnamed: C19.1, U3.2 (CAP+)
unnamed: C19.2, U3.4 (CAP-)
RESET: AD2S1205.33 (~RESET), R11.2, U1.2 (RESET*)
SIN+: AD2S1205.37 (SIN), J1.4, R4.2
SIN-: AD2S1205.38 (SINLO), J1.3, R4.1
Vamp+: C14.2, C15.2, C16.2, C17.2, C20.2, J2.4, R9.2, U2.8 (V+), U3.8 (V+), U4.1 (IN)
Vamp-: C21.2, R20.2, U3.5 (VOUT)
Vref: C13.2, R9.1, R10.2, U2.3 (+IN_1), U2.5 (+IN_2)
